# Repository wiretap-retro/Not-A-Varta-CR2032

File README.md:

# Not-A-Varta CR2032
Similar to the "Not-A-Varta", but with a vertical CR2032 holder, and elongated mounting holes.

## Info
Same concept as the Not-A-Varta, except with a vertical CR2032 holder and elongated mounting holes for better fit across various motherboards which can have anywhere from 18-20mm pin spacing.
\
\
Original CR1220 version here: https://github.com/wiretap-retro/Not-A-Varta
\
\
Open hardware design. Feel free to do what you want with it.

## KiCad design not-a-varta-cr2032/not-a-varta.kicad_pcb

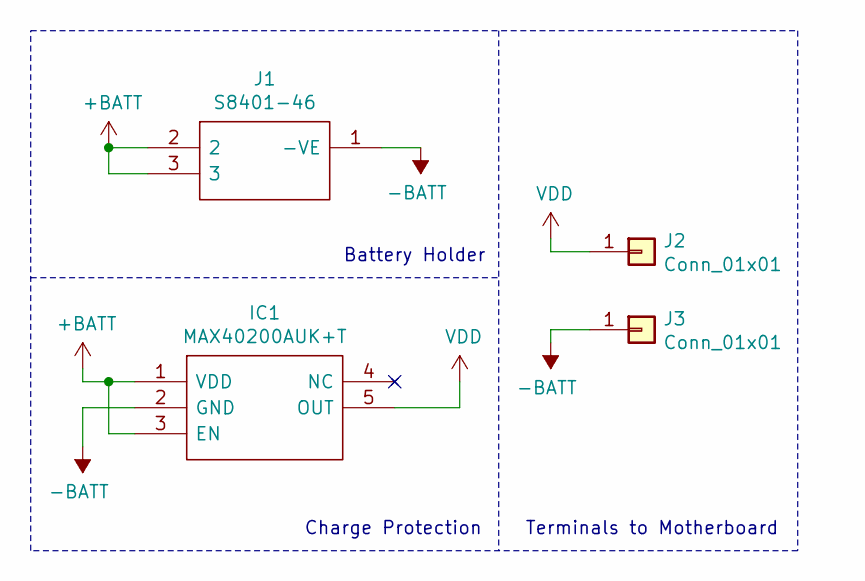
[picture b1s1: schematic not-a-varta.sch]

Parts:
IC1: MAX40200AUK+T; SOT95P280X145-5N; Mouser Part Number 700-MAX40200AUK+T
J1: S8401-46; Mouser Part Number 855-S8401-46
J2, J3: Conn_01x01; PinHeader_1x01_P2.54mm_Vertical

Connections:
+BATT: IC1.1 (VDD), IC1.3 (EN), J1.2, J1.3
-BATT: IC1.2 (GND), J1.1 (-VE), J3.1
VDD: IC1.5 (OUT), J2.1

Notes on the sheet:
Charge Protection
Battery Holder
Terminals to Motherboard

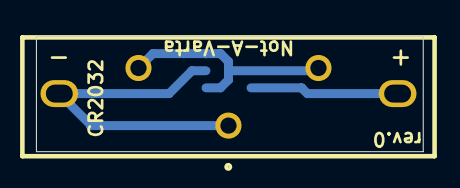
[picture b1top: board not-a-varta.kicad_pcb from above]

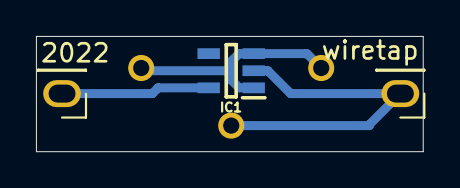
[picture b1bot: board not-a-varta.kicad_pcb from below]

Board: 2 copper layers, 21.5 x 6.4 mm, 4 parts (3 on the bottom side), 3 nets.

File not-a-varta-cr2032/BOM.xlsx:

Reference | Value | Footprint | Description | Manufacturer Name | Manufacturer Part Number
IC1 | MAX40200AUK+T | SOT95P280X145-5N | OR Controller Source Selector Switch P-Channel 1:1 SOT-23-5 | Maxim Integrated | MAX40200AUK+T
J1 | S8401-46 | S8401-46 | HARWIN - S8401-46 - HOLDER, EZ-COIN, CR/BR2032 CELLS | Harwin | S8401-46
J2 | Conn_01x01 | Connector_PinHeader_2.54mm:PinHeader_1x01_P2.54mm_Vertical
J3 | Conn_01x01 | Connector_PinHeader_2.54mm:PinHeader_1x01_P2.54mm_Vertical
